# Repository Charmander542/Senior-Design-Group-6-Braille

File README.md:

# Senior Design Group 6 - Braille Project

Welcome to the EC463 Senior Design Group 6 Braille project repository.

Main Google Doc before README migration: https://docs.google.com/document/d/1c1Lonarr0yz-ggmuZfPKdth9k53kwFiAMk2oVoeEsT8/edit?usp=sharing

## Project Structure

### 📁 `electrical/`
Contains hardware-related files including:
- **driver.cpp**: Driver code for hardware control
- **pcb/**: PCB design files
  - `conductors/`: Braille cell conductor board designs (KiCad files)
  - `controller/`: Braille cell controller board designs (KiCad files)
  - `devboard/`: Development board schematics

### 📚 `braille_converter/`
A Python library for converting text to 6-dot braille representation.

**Features:**
- ✨ Convert text to Unicode braille characters
- 📁 Convert entire text files to braille
- 🔍 Detailed character-by-character analysis
- 📊 Visual dot pattern representation
- 🎯 Full support for letters, numbers, punctuation, and symbols

**Quick Start:**
```python
from braille_converter import text_to_braille

text = "Hello World!"
braille = text_to_braille(text)
print(braille)  # Output: ⠠⠓⠑⠇⠇⠕⠀⠠⠺⠕⠗⠇⠙⠖
```

**Documentation:**
- [Full README](braille_converter/README.md) - Complete API documentation
- [Quick Start Guide](braille_converter/QUICKSTART.md) - Get started in 5 minutes
- [Examples](braille_converter/examples/) - Working code examples

**Try it now:**
```bash
cd braille_converter
python demo.py
```

### 🤖 `braille_converter/arduino_library/`
**NEW!** Arduino C++ library for on-device 8-dot Braille conversion - no Python required!

**Features:**
- ⚡ Native Arduino C++ implementation
- 8️⃣ Full 8-dot Braille support (2x4 grid)
- 🔌 Direct hardware control - no computer needed
- 💾 Memory efficient - runs on Arduino Uno
- 🎯 Complete ASCII character set
- 📚 Multiple examples included

**Quick Start:**
```cpp
#include <BrailleConverter.h>

BrailleConverter converter;

void setup() {
  Serial.begin(115200);
  BrailleChar bc = converter.convertChar('A');
  // bc.dots = {1, 7} - ready to drive hardware!
}
```

**Documentation:**
- [Arduino Library README](braille_converter/arduino_library/README.md) - Complete guide
- [Installation Guide](braille_converter/arduino_library/INSTALLATION.md) - Setup instructions
- [Quick Reference](braille_converter/arduino_library/QUICK_REFERENCE.md) - API cheat sheet
- [Examples](braille_converter/arduino_library/examples/) - 4 working examples

### 🔌 `braille_converter/arduino_integration/`
Arduino integration for sending braille patterns to hardware over serial.

**Features:**
- 🔌 Serial communication with Arduino
- 📡 Send braille dot patterns to hardware
- 🎮 Interactive and command-line interfaces
- 🧪 Comprehensive test suite
- 📖 Full examples and documentation

**Quick Test:**
```bash
# Install PySerial
pip install pyserial

# Upload arduino_receiver.ino to your Arduino

# Run interactive mode
cd braille_converter/arduino_integration
python braille_to_arduino.py
```

**Documentation:**
- [Arduino Integration README](braille_converter/arduino_integration/README.md) - Complete guide
- Arduino sketch included (`arduino_receiver.ino`)
- 10+ working examples

## Getting Started

### For Software Development (Braille Converter)
```bash
# Install the library
pip install -e braille_converter

# Run the demo
cd braille_converter
python demo.py

# Run examples
cd braille_converter/examples
python basic_usage.py
python file_conversion.py
```

### For Arduino Integration (Python-based)
```bash
# Install PySerial
pip install pyserial

# 1. Upload arduino_receiver.ino to your Arduino using Arduino IDE

# 2. Find your Arduino port
cd braille_converter/arduino_integration
python braille_to_arduino.py --list

# 3. Run interactive mode
python braille_to_arduino.py

# 4. Or run test suite
python test_arduino.py

# 5. Or run examples
python examples.py
```

See [Arduino Integration README](braille_converter/arduino_integration/README.md) for detailed setup.

### For Arduino Library (Native C++ - No Python Required!)
```bash
# 1. Copy arduino_library folder to Arduino libraries directory
cp -r braille_converter/arduino_library ~/Documents/Arduino/libraries/BrailleConverter

# 2. Restart Arduino IDE

# 3. Open example: File → Examples → BrailleConverter → BasicConversion

# 4. Upload to your Arduino and open Serial Monitor (115200 baud)
```

See [Arduino Library Installation](braille_converter/arduino_library/INSTALLATION.md) for detailed setup.

### For Hardware Development
Navigate to the `electrical/` directory to access:
- PCB design files (KiCad format)
- Hardware driver code
- Development board schematics

## Team

EC463 Senior Design - Group 6

## License

This project is part of the EC463 Senior Design course.

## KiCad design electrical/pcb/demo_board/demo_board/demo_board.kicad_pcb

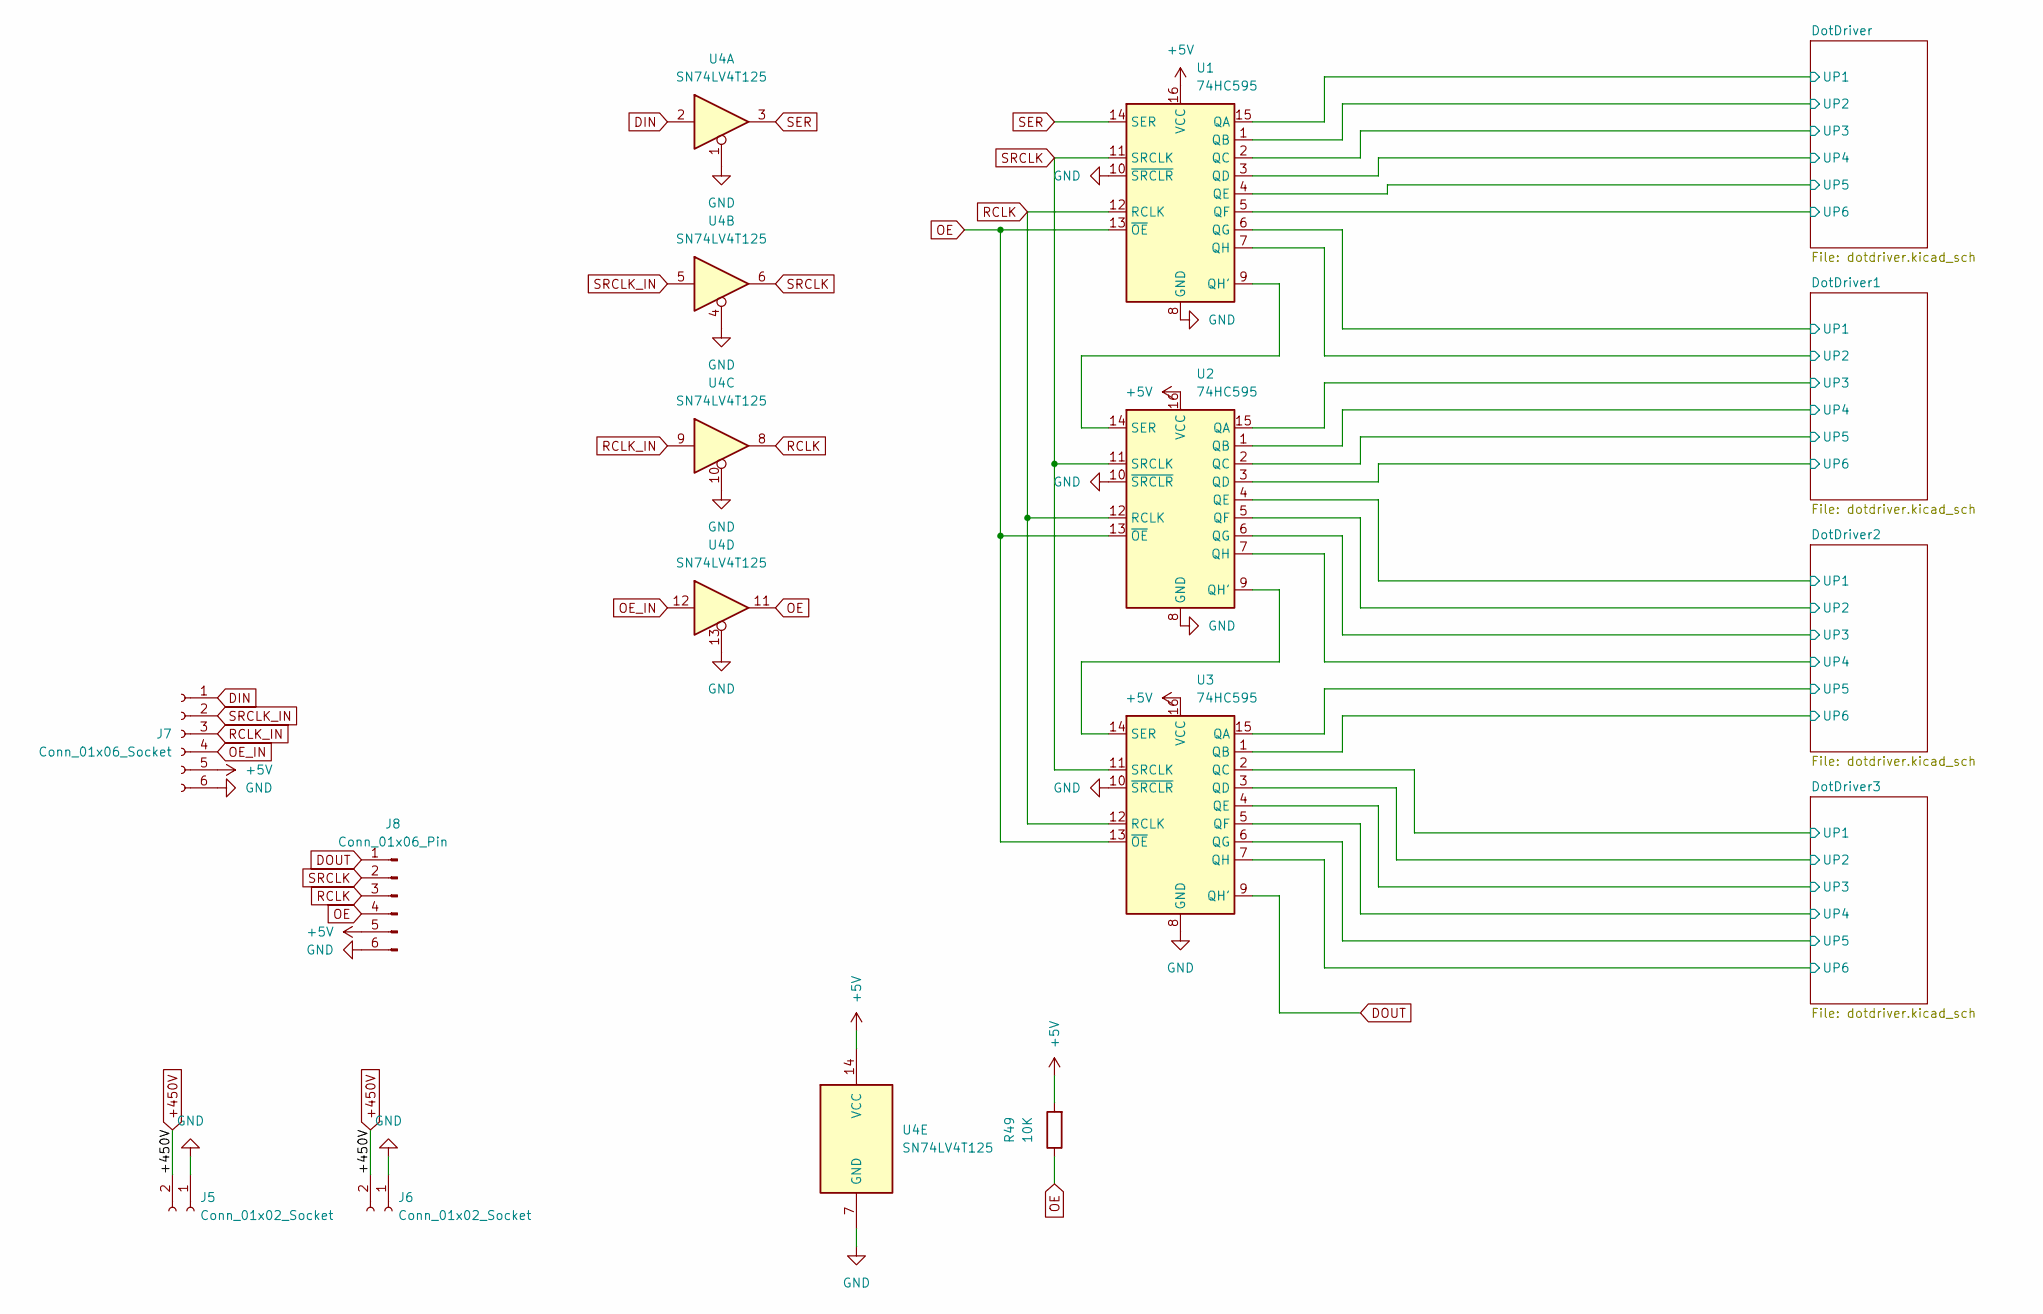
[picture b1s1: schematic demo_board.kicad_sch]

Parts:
J5, J6: Conn_01x02_Socket; AMASS_XT60-M_1x02_P7.20mm_Vertical
J7: Conn_01x06_Socket; PinSocket_2x03_P2.54mm_Horizontal
J8: Conn_01x06_Pin; PinHeader_2x03_P2.54mm_Horizontal
R49: 10K; R_0603_1608Metric
U1, U2, U3: 74HC595; SOIC-16W_5.3x10.2mm_P1.27mm
U4: SN74LV4T125; TSSOP-14_4.4x5mm_P0.65mm

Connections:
+5V: J7.5, J8.5, R49.2, U1.16 (VCC), U2.16 (VCC), U3.16 (VCC), U4.14 (VCC)
+450V: J5.2, J6.2; also elsewhere on the board
/DotDriver1/UP1: U1.6 (QG); also elsewhere on the board
/DotDriver1/UP2: U1.7 (QH); also elsewhere on the board
/DotDriver1/UP3: U2.15 (QA); also elsewhere on the board
/DotDriver1/UP4: U2.1 (QB); also elsewhere on the board
/DotDriver1/UP5: U2.2 (QC); also elsewhere on the board
/DotDriver1/UP6: U2.3 (QD); also elsewhere on the board
/DotDriver2/UP1: U2.4 (QE); also elsewhere on the board
/DotDriver2/UP2: U2.5 (QF); also elsewhere on the board
/DotDriver2/UP3: U2.6 (QG); also elsewhere on the board
/DotDriver2/UP4: U2.7 (QH); also elsewhere on the board
/DotDriver2/UP5: U3.15 (QA); also elsewhere on the board
/DotDriver2/UP6: U3.1 (QB); also elsewhere on the board
/DotDriver3/UP1: U3.2 (QC); also elsewhere on the board
/DotDriver3/UP2: U3.3 (QD); also elsewhere on the board
/DotDriver3/UP3: U3.4 (QE); also elsewhere on the board
/DotDriver3/UP4: U3.5 (QF); also elsewhere on the board
/DotDriver3/UP5: U3.6 (QG); also elsewhere on the board
/DotDriver3/UP6: U3.7 (QH); also elsewhere on the board
/DotDriver/UP1: U1.15 (QA); also elsewhere on the board
/DotDriver/UP2: U1.1 (QB); also elsewhere on the board
/DotDriver/UP3: U1.2 (QC); also elsewhere on the board
/DotDriver/UP4: U1.3 (QD); also elsewhere on the board
/DotDriver/UP5: U1.4 (QE); also elsewhere on the board
/DotDriver/UP6: U1.5 (QF); also elsewhere on the board
DIN: J7.1, U4.2
DOUT: J8.1, U3.9 (QH')
GND: J5.1, J6.1, J7.6, J8.6, U1.8 (GND), U1.10 (~SRCLR), U2.8 (GND), U2.10 (~SRCLR), U3.8 (GND), U3.10 (~SRCLR), U4.1, U4.4, U4.7 (GND), U4.10, U4.13; also elsewhere on the board
unnamed: U1.9 (QH'), U2.14 (SER)
unnamed: U2.9 (QH'), U3.14 (SER)
OE: J8.4, R49.1, U1.13 (~OE), U2.13 (~OE), U3.13 (~OE), U4.11
OE_IN: J7.4, U4.12
RCLK: J8.3, U1.12 (RCLK), U2.12 (RCLK), U3.12 (RCLK), U4.8
RCLK_IN: J7.3, U4.9
SER: U1.14 (SER), U4.3
SRCLK: J8.2, U1.11 (SRCLK), U2.11 (SRCLK), U3.11 (SRCLK), U4.6
SRCLK_IN: J7.2, U4.5

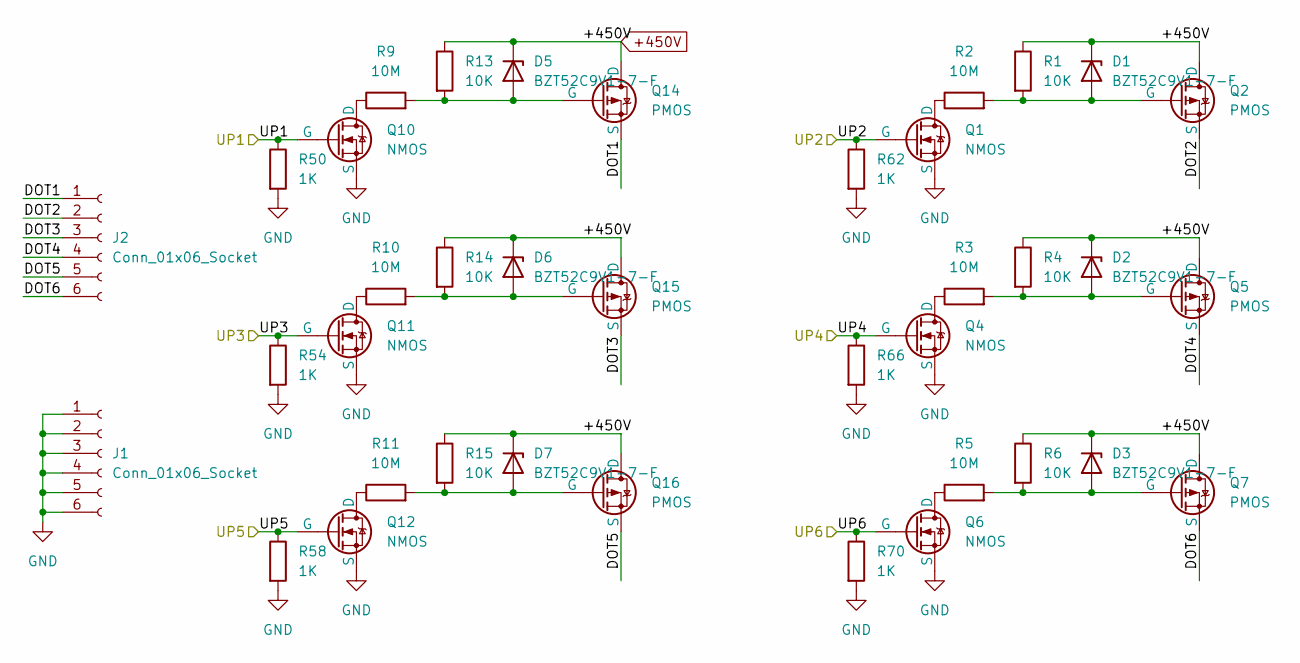
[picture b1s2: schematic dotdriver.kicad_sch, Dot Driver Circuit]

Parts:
D1, D2, D3, D5, D6, D7: BZT52C9V1-7-F; D_SOD-123
J1, J2: Conn_01x06_Socket; PinSocket_2x03_P2.54mm_Vertical
Q1, Q4, Q6, Q10, Q11, Q12: NMOS; SOT-89-3
Q2, Q5, Q7, Q14, Q15, Q16: PMOS; SOT-89-3
R1, R4, R6, R13, R14, R15: 10K; R_0603_1608Metric
R2, R3, R5, R9, R10, R11: 10M; R_0603_1608Metric
R50, R54, R58, R62, R66, R70: 1K; R_0603_1608Metric

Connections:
+450V: D1.1 (K), D2.1 (K), D3.1 (K), D5.1 (K), D6.1 (K), D7.1 (K), Q2.1 (D), Q5.1 (D), Q7.1 (D), Q14.1 (D), Q15.1 (D), Q16.1 (D), R1.1, R4.1, R6.1, R13.1, R14.1, R15.1; also elsewhere on the board
/DotDriver/DOT1: J2.1, Q14.3 (S)
/DotDriver/DOT2: J2.2, Q2.3 (S)
/DotDriver/DOT3: J2.3, Q15.3 (S)
/DotDriver/DOT4: J2.4, Q5.3 (S)
/DotDriver/DOT5: J2.5, Q16.3 (S)
/DotDriver/DOT6: J2.6, Q7.3 (S)
/DotDriver/UP1: Q10.2 (G), R50.1; also elsewhere on the board
/DotDriver/UP2: Q1.2 (G), R62.1; also elsewhere on the board
/DotDriver/UP3: Q11.2 (G), R54.1; also elsewhere on the board
/DotDriver/UP4: Q4.2 (G), R66.1; also elsewhere on the board
/DotDriver/UP5: Q12.2 (G), R58.1; also elsewhere on the board
/DotDriver/UP6: Q6.2 (G), R70.1; also elsewhere on the board
GND: J1.1, J1.2, J1.3, J1.4, J1.5, J1.6, Q1.3 (S), Q4.3 (S), Q6.3 (S), Q10.3 (S), Q11.3 (S), Q12.3 (S), R50.2, R54.2, R58.2, R62.2, R66.2, R70.2; also elsewhere on the board
unnamed: D1.2 (A), Q2.2 (G), R1.2, R2.2
unnamed: D2.2 (A), Q5.2 (G), R3.2, R4.2
unnamed: D3.2 (A), Q7.2 (G), R5.2, R6.2
unnamed: D5.2 (A), Q14.2 (G), R9.2, R13.2
unnamed: D6.2 (A), Q15.2 (G), R10.2, R14.2
unnamed: D7.2 (A), Q16.2 (G), R11.2, R15.2
unnamed: Q1.1 (D), R2.1
unnamed: Q4.1 (D), R3.1
unnamed: Q6.1 (D), R5.1
unnamed: Q10.1 (D), R9.1
unnamed: Q11.1 (D), R10.1
unnamed: Q12.1 (D), R11.1

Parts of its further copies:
D4, D8, D9, D10, D11, D12, D13, D14, D15, D16, D17, D18, D19, D20, D21, D22, D23, D24: BZT52C9V1-7-F; D_SOD-123
J0, J3, J4, J9, J10, J11: Conn_01x06_Socket; PinSocket_2x03_P2.54mm_Vertical
Q3, Q8, Q9, Q19, Q20, Q21, Q25, Q26, Q27, Q31, Q32, Q33, Q37, Q38, Q39, Q43, Q44, Q45: NMOS; SOT-89-3
Q13, Q17, Q18, Q22, Q23, Q24, Q28, Q29, Q30, Q34, Q35, Q36, Q40, Q41, Q42, Q46, Q47, Q48: PMOS; SOT-89-3
R7, R8, R12, R19, R20, R21, R25, R26, R27, R31, R32, R33, R37, R38, R39, R43, R44, R45: 10M; R_0603_1608Metric
R16, R17, R18, R22, R23, R24, R28, R29, R30, R34, R35, R36, R40, R41, R42, R46, R47, R48: 10K; R_0603_1608Metric
R51, R52, R53, R55, R56, R57, R59, R60, R61, R63, R64, R65, R67, R68, R69, R71, R72, R73: 1K; R_0603_1608Metric

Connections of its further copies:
+450V: D4.1 (K), D8.1 (K), D9.1 (K), D10.1 (K), D11.1 (K), D12.1 (K), D13.1 (K), D14.1 (K), D15.1 (K), D16.1 (K), D17.1 (K), D18.1 (K), D19.1 (K), D20.1 (K), D21.1 (K), D22.1 (K), D23.1 (K), D24.1 (K), Q13.1 (D), Q17.1 (D), Q18.1 (D), Q22.1 (D), Q23.1 (D), Q24.1 (D), Q28.1 (D), Q29.1 (D), Q30.1 (D), Q34.1 (D), Q35.1 (D), Q36.1 (D), Q40.1 (D), Q41.1 (D), Q42.1 (D), Q46.1 (D), Q47.1 (D), Q48.1 (D), R16.1, R17.1, R18.1, R22.1, R23.1, R24.1, R28.1, R29.1, R30.1, R34.1, R35.1, R36.1, R40.1, R41.1, R42.1, R46.1, R47.1, R48.1; also elsewhere on the board
/DotDriver1/DOT1: J0.1, Q13.3 (S)
/DotDriver1/DOT2: J0.2, Q22.3 (S)
/DotDriver1/DOT3: J0.3, Q17.3 (S)
/DotDriver1/DOT4: J0.4, Q23.3 (S)
/DotDriver1/DOT5: J0.5, Q18.3 (S)
/DotDriver1/DOT6: J0.6, Q24.3 (S)
/DotDriver1/UP1: Q3.2 (G), R51.1; also elsewhere on the board
/DotDriver1/UP2: Q19.2 (G), R63.1; also elsewhere on the board
/DotDriver1/UP3: Q8.2 (G), R55.1; also elsewhere on the board
/DotDriver1/UP4: Q20.2 (G), R67.1; also elsewhere on the board
/DotDriver1/UP5: Q9.2 (G), R59.1; also elsewhere on the board
/DotDriver1/UP6: Q21.2 (G), R71.1; also elsewhere on the board
/DotDriver2/DOT1: J3.1, Q28.3 (S)
/DotDriver2/DOT2: J3.2, Q34.3 (S)
/DotDriver2/DOT3: J3.3, Q29.3 (S)
/DotDriver2/DOT4: J3.4, Q35.3 (S)
/DotDriver2/DOT5: J3.5, Q30.3 (S)
/DotDriver2/DOT6: J3.6, Q36.3 (S)
/DotDriver2/UP1: Q25.2 (G), R52.1; also elsewhere on the board
/DotDriver2/UP2: Q31.2 (G), R64.1; also elsewhere on the board
/DotDriver2/UP3: Q26.2 (G), R56.1; also elsewhere on the board
/DotDriver2/UP4: Q32.2 (G), R68.1; also elsewhere on the board
/DotDriver2/UP5: Q27.2 (G), R60.1; also elsewhere on the board
/DotDriver2/UP6: Q33.2 (G), R72.1; also elsewhere on the board
/DotDriver3/DOT1: J4.1, Q40.3 (S)
/DotDriver3/DOT2: J4.2, Q46.3 (S)
/DotDriver3/DOT3: J4.3, Q41.3 (S)
/DotDriver3/DOT4: J4.4, Q47.3 (S)
/DotDriver3/DOT5: J4.5, Q42.3 (S)
/DotDriver3/DOT6: J4.6, Q48.3 (S)
/DotDriver3/UP1: Q37.2 (G), R53.1; also elsewhere on the board
/DotDriver3/UP2: Q43.2 (G), R65.1; also elsewhere on the board
/DotDriver3/UP3: Q38.2 (G), R57.1; also elsewhere on the board
/DotDriver3/UP4: Q44.2 (G), R69.1; also elsewhere on the board
/DotDriver3/UP5: Q39.2 (G), R61.1; also elsewhere on the board
/DotDriver3/UP6: Q45.2 (G), R73.1; also elsewhere on the board
GND: J9.1, J9.2, J9.3, J9.4, J9.5, J9.6, J10.1, J10.2, J10.3, J10.4, J10.5, J10.6, J11.1, J11.2, J11.3, J11.4, J11.5, J11.6, Q3.3 (S), Q8.3 (S), Q9.3 (S), Q19.3 (S), Q20.3 (S), Q21.3 (S), Q25.3 (S), Q26.3 (S), Q27.3 (S), Q31.3 (S), Q32.3 (S), Q33.3 (S), Q37.3 (S), Q38.3 (S), Q39.3 (S), Q43.3 (S), Q44.3 (S), Q45.3 (S), R51.2, R52.2, R53.2, R55.2, R56.2, R57.2, R59.2, R60.2, R61.2, R63.2, R64.2, R65.2, R67.2, R68.2, R69.2, R71.2, R72.2, R73.2; also elsewhere on the board
unnamed: D4.2 (A), Q13.2 (G), R7.2, R16.2
unnamed: D8.2 (A), Q17.2 (G), R8.2, R17.2
unnamed: D9.2 (A), Q18.2 (G), R12.2, R18.2
unnamed: D10.2 (A), Q22.2 (G), R19.2, R22.2
unnamed: D11.2 (A), Q23.2 (G), R20.2, R23.2
unnamed: D12.2 (A), Q24.2 (G), R21.2, R24.2
unnamed: D13.2 (A), Q28.2 (G), R25.2, R28.2
unnamed: D14.2 (A), Q29.2 (G), R26.2, R29.2
unnamed: D15.2 (A), Q30.2 (G), R27.2, R30.2
unnamed: D16.2 (A), Q34.2 (G), R31.2, R34.2
unnamed: D17.2 (A), Q35.2 (G), R32.2, R35.2
unnamed: D18.2 (A), Q36.2 (G), R33.2, R36.2
unnamed: D19.2 (A), Q40.2 (G), R37.2, R40.2
unnamed: D20.2 (A), Q41.2 (G), R38.2, R41.2
unnamed: D21.2 (A), Q42.2 (G), R39.2, R42.2
unnamed: D22.2 (A), Q46.2 (G), R43.2, R46.2
unnamed: D23.2 (A), Q47.2 (G), R44.2, R47.2
unnamed: D24.2 (A), Q48.2 (G), R45.2, R48.2
unnamed: Q3.1 (D), R7.1
unnamed: Q8.1 (D), R8.1
unnamed: Q9.1 (D), R12.1
unnamed: Q19.1 (D), R19.1
unnamed: Q20.1 (D), R20.1
unnamed: Q21.1 (D), R21.1
unnamed: Q25.1 (D), R25.1
unnamed: Q26.1 (D), R26.1
unnamed: Q27.1 (D), R27.1
unnamed: Q31.1 (D), R31.1
unnamed: Q32.1 (D), R32.1
unnamed: Q33.1 (D), R33.1
unnamed: Q37.1 (D), R37.1
unnamed: Q38.1 (D), R38.1
unnamed: Q39.1 (D), R39.1
unnamed: Q43.1 (D), R43.1
unnamed: Q44.1 (D), R44.1
unnamed: Q45.1 (D), R45.1

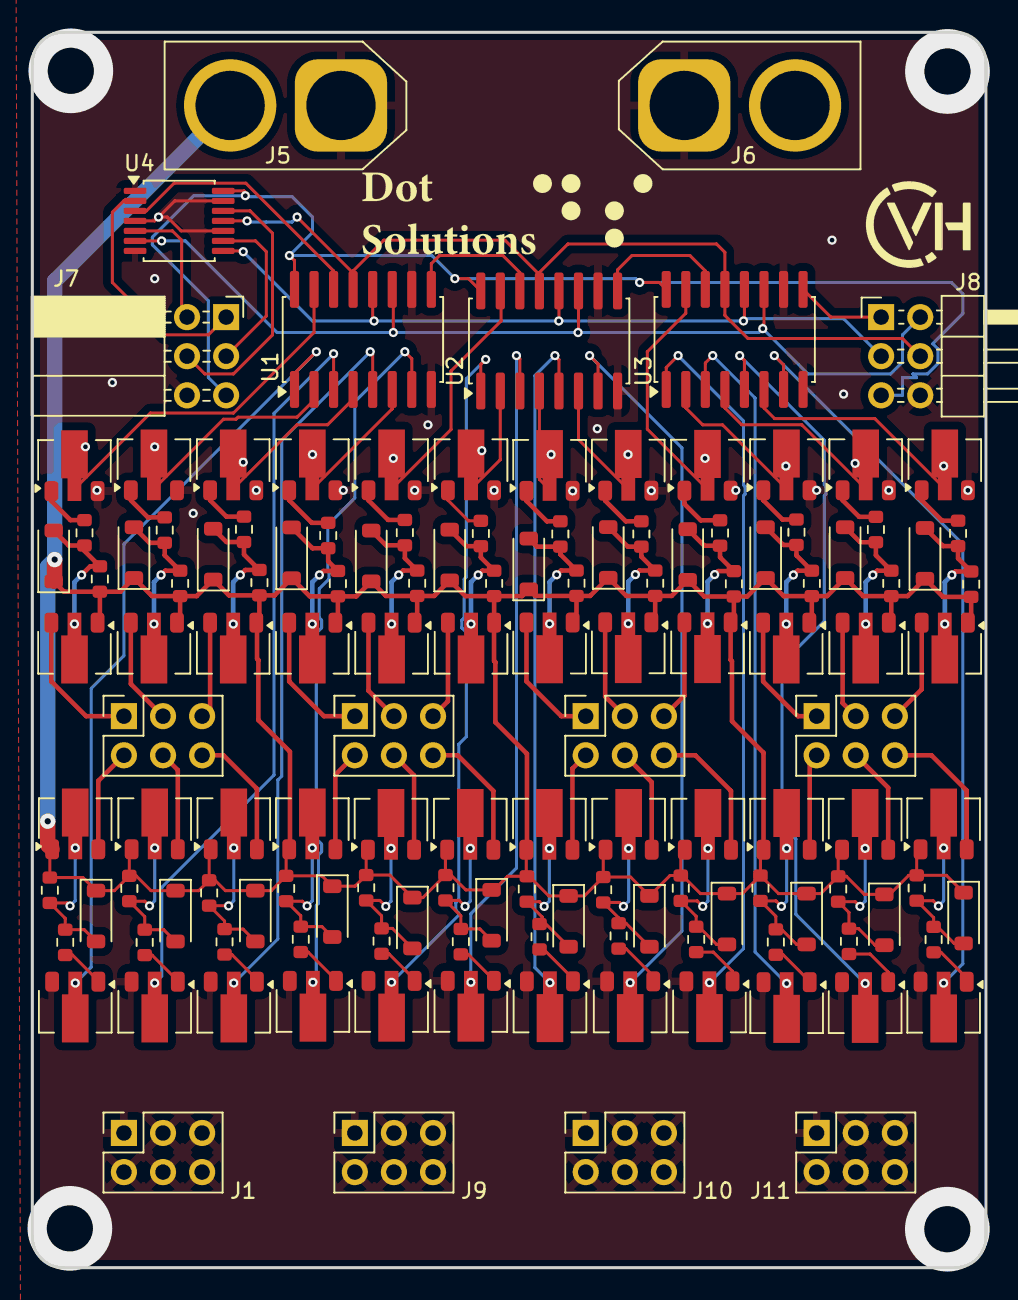
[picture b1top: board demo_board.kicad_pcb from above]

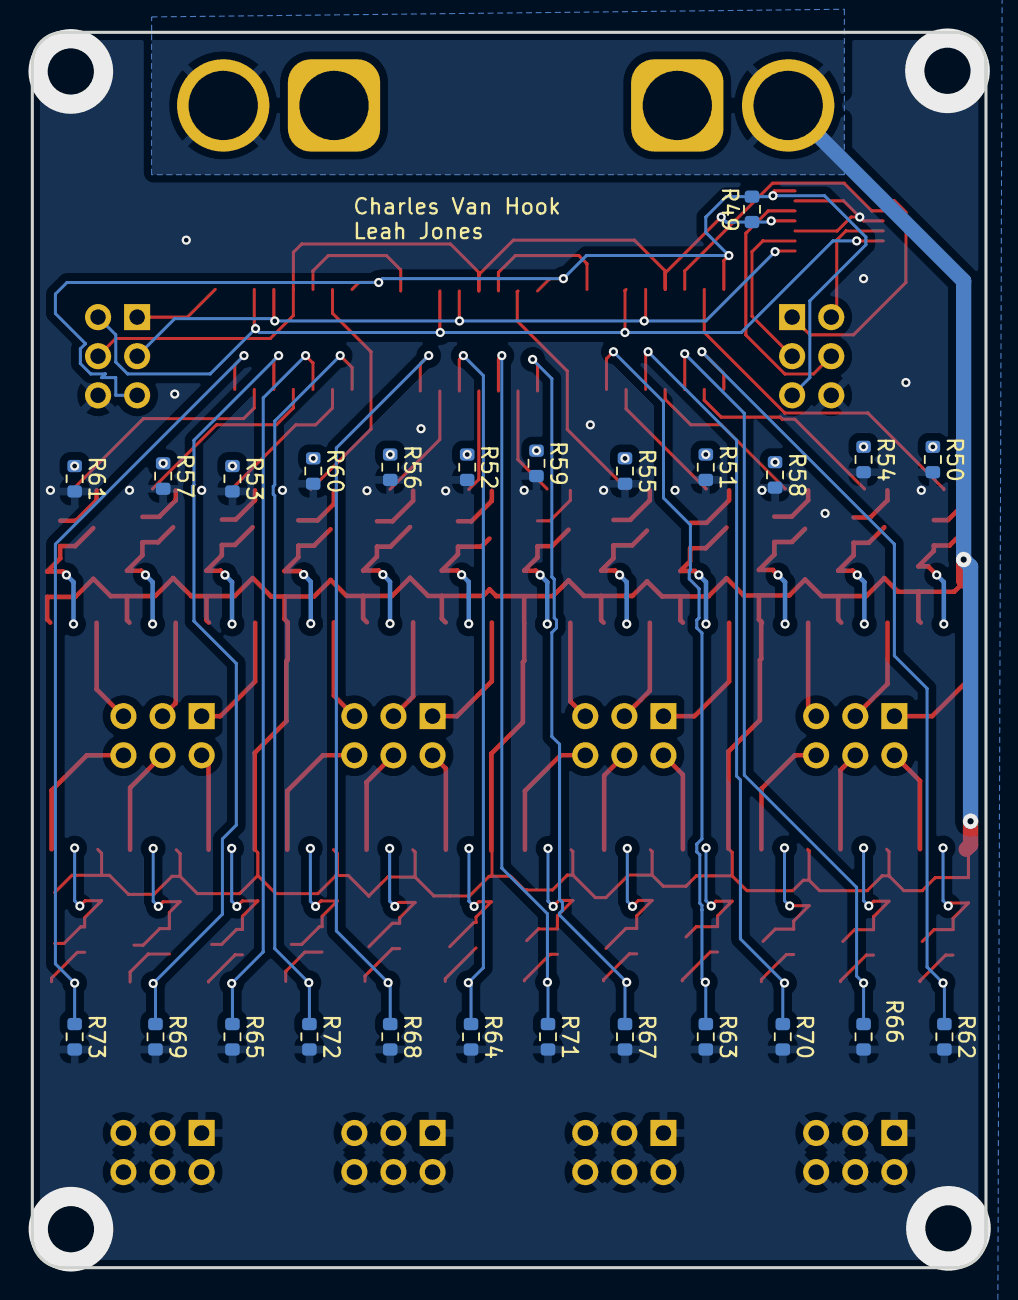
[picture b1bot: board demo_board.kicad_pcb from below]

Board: 2 copper layers, 62.0 x 80.2 mm, 161 parts (25 on the bottom side), 110 nets.

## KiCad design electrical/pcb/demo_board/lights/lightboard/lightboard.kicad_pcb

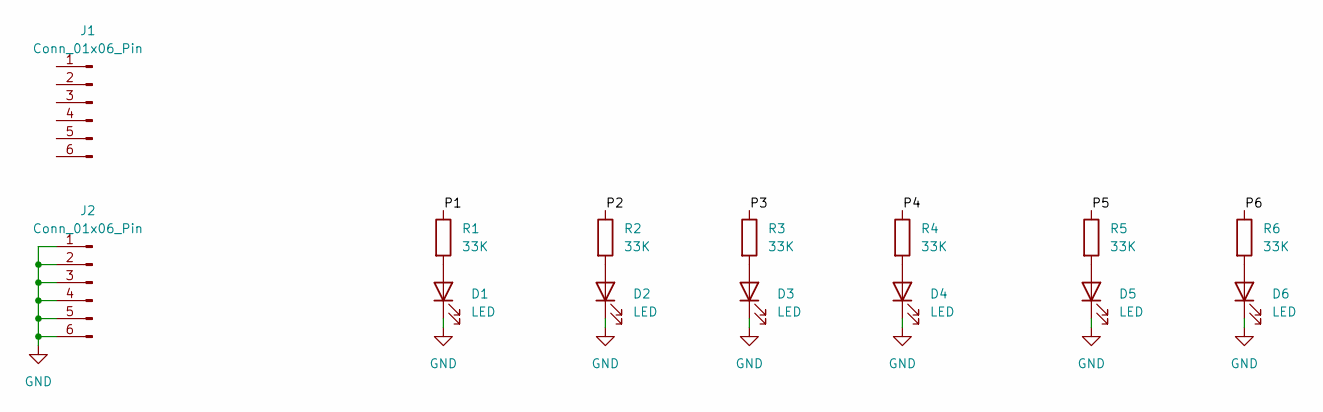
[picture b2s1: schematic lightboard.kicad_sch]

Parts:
D1, D2, D3, D4, D5, D6: LED; LED_0805_2012Metric
J1, J2: Conn_01x06_Pin
R1, R2, R3, R4, R5, R6: 33K; R_1210_3225Metric

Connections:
/P1: J1.6, R1.1
/P2: J1.1, R2.1
/P3: J1.3, R3.1
/P4: J1.4, R4.1
/P5: J1.2, R5.1
/P6: J1.5, R6.1
GND: D1.1 (K), D2.1 (K), D3.1 (K), D4.1 (K), D5.1 (K), D6.1 (K), J2.1, J2.2, J2.3, J2.4, J2.5, J2.6
unnamed: D1.2 (A), R1.2
unnamed: D2.2 (A), R2.2
unnamed: D3.2 (A), R3.2
unnamed: D4.2 (A), R4.2
unnamed: D5.2 (A), R5.2
unnamed: D6.2 (A), R6.2

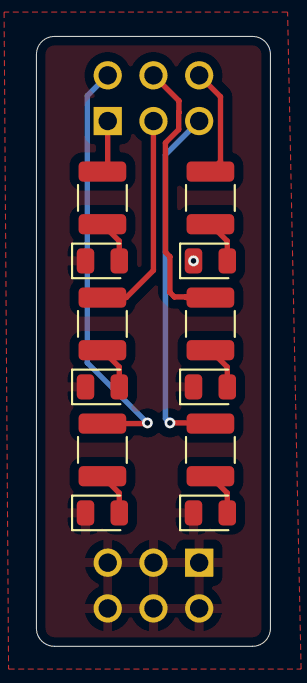
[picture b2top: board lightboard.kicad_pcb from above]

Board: 2 copper layers, 13.0 x 33.9 mm, 14 parts (0 on the bottom side), 13 nets.

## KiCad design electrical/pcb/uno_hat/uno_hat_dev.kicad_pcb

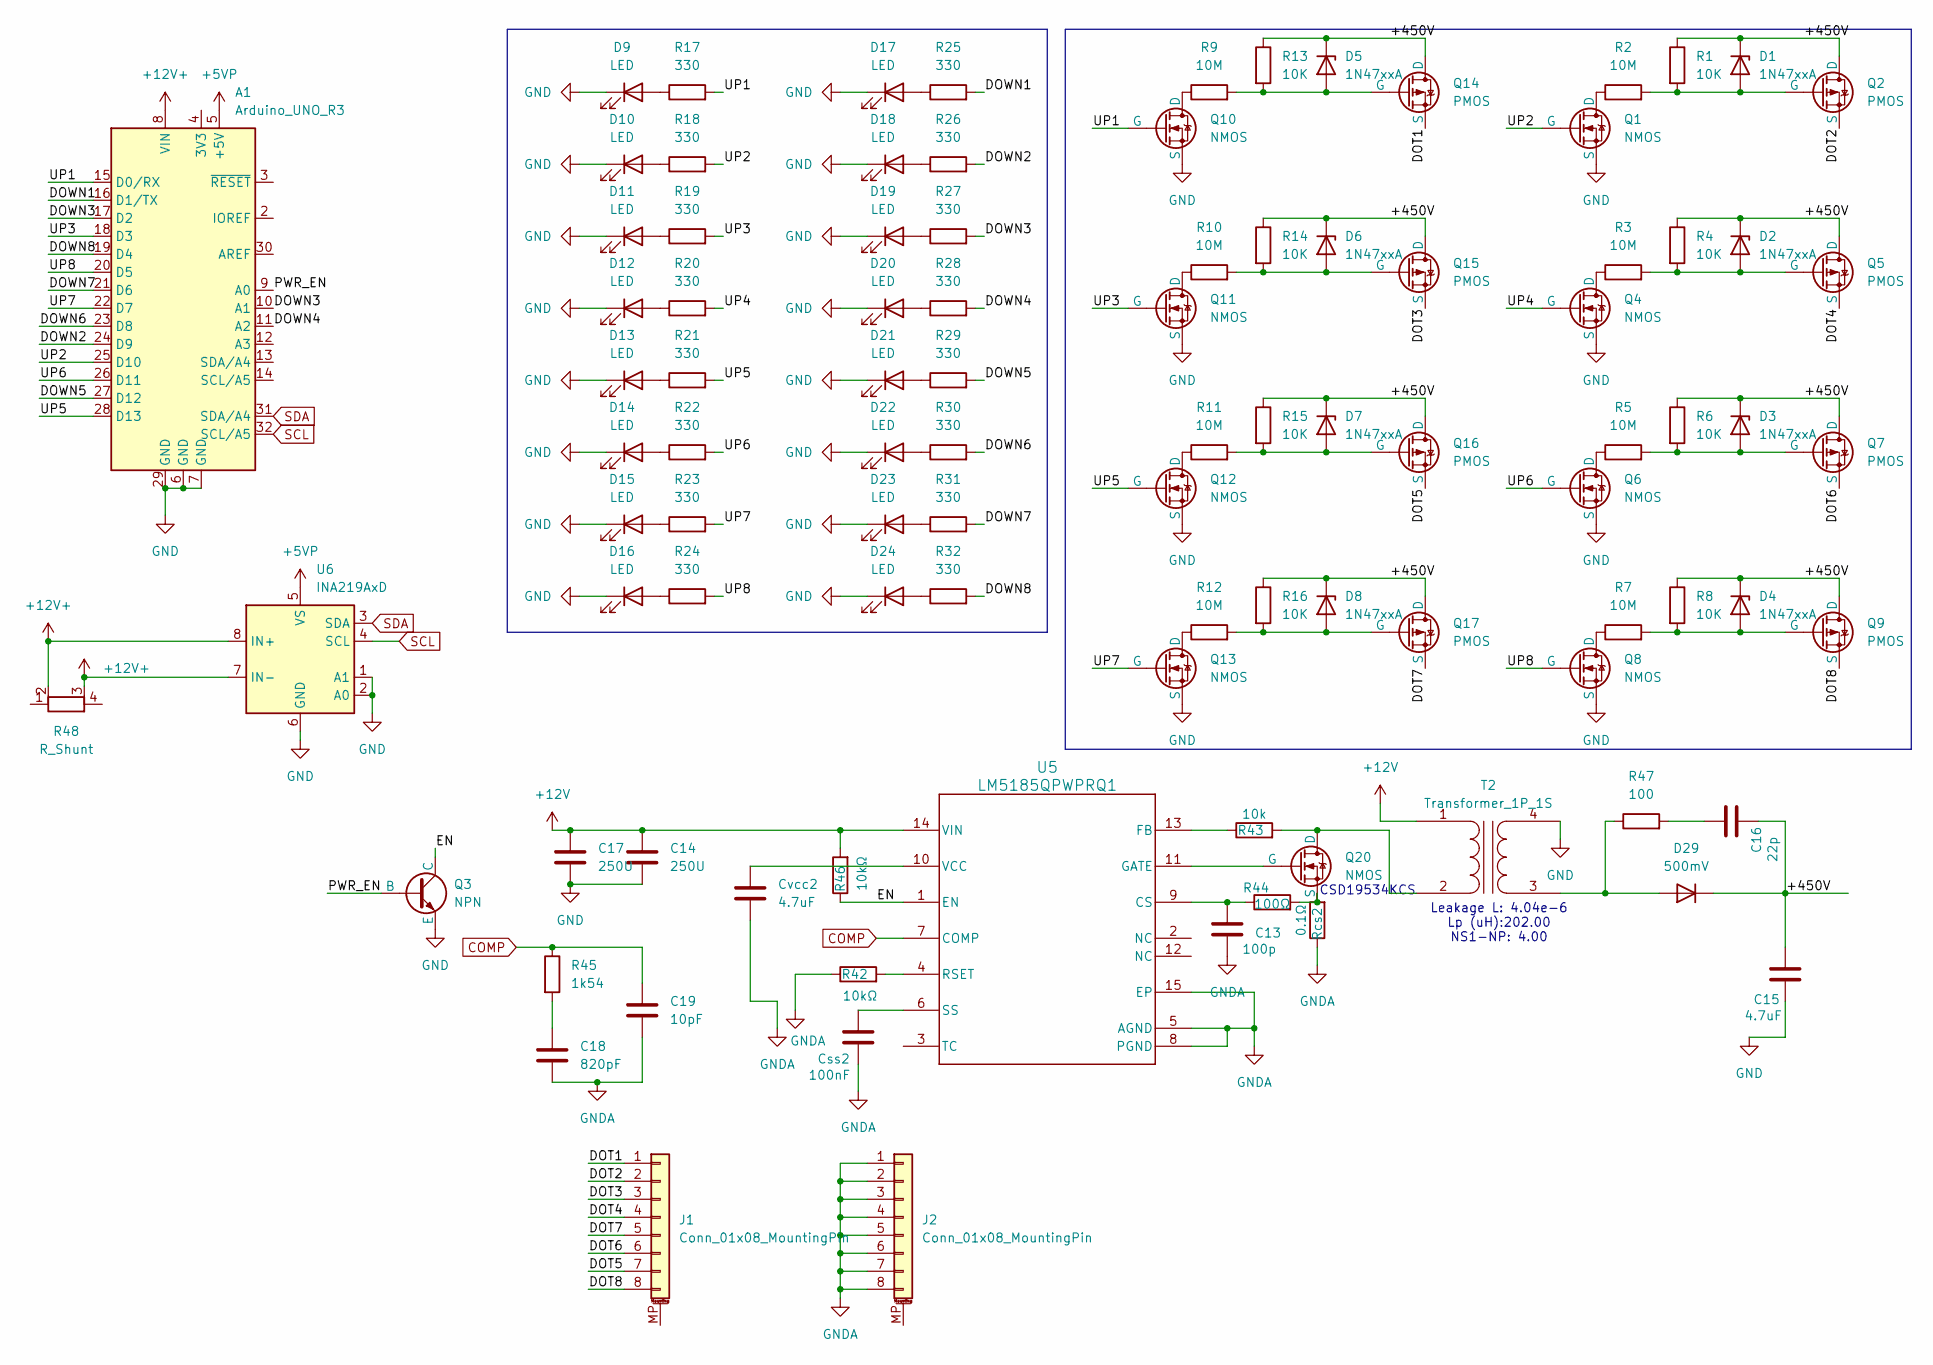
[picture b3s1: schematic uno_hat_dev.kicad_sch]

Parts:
A1: Arduino_UNO_R3
C13: 100p; R_0805_2012Metric
C14, C17: 250U; CP_Radial_Tantal_D8.0mm_P2.50mm
C15: 4.7uF; R_0805_2012Metric
C16: 22p; R_0805_2012Metric
C18: 820pF; R_0805_2012Metric
C19: 10pF; R_0805_2012Metric
Css2: 100nF; R_0805_2012Metric
Cvcc2: 4.7uF; R_0805_2012Metric
D1, D2, D3, D4, D5, D6, D7, D8: 1N47xxA; D_DO-41_SOD81_P10.16mm_Horizontal
D9, D10, D11, D12, D13, D14, D15, D16, D17, D18, D19, D20, D21, D22, D23, D24: LED; LED_0805_2012Metric
D29: 500mV; D_A-405_P12.70mm_Horizontal
J1, J2: Conn_01x08_MountingPin; Amphenol_F32Q-1A7x1-11008_1x08-1MP_P0.5mm_Horizontal
Q1, Q4, Q6, Q8, Q10, Q11, Q12, Q13: NMOS; TO-92_Inline
Q2, Q5, Q7, Q9, Q14, Q15, Q16, Q17: PMOS; TO-92_Inline
Q3: NPN; TO-92_Inline
Q20: NMOS; TO-220-3_Vertical
R1, R4, R6, R8, R13, R14, R15, R16: 10K; R_Axial_DIN0207_L6.3mm_D2.5mm_P7.62mm_Horizontal
R2, R3, R5, R7, R9, R10, R11, R12: 10M; R_Axial_DIN0207_L6.3mm_D2.5mm_P7.62mm_Horizontal
R17, R18, R19, R20, R21, R22, R23, R24, R25, R26, R27, R28, R29, R30, R31, R32: 330; R_0805_2012Metric
R42, R46: 10kΩ; R_0805_2012Metric
R43: 10k; R_0805_2012Metric
R44: 100Ω; R_0805_2012Metric
R45: 1k54; R_0805_2012Metric
R47: 100; R_0805_2012Metric
R48: R_Shunt; R_Shunt_Ohmite_LVK24
Rcs2: 0.1Ω; R_0805_2012Metric
T2: Transformer_1P_1S; PinSocket_1x04_P2.54mm_Vertical
U5: LM5185QPWPRQ1; Texas_HTSSOP-14-1EP_4.4x5mm_P0.65mm_EP3.4x5mm_Mask3.155x3.2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
U6: INA219AxD; SOIC-8_3.9x4.9mm_P1.27mm

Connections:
+5VP: A1.5 (+5V), U6.5 (VS)
+12V: C14.1, C17.1, R46.2, T2.1 (AA), U5.14 (VIN)
+12V+: A1.8 (VIN), R48.2, R48.3, U6.7 (IN-), U6.8 (IN+)
/+450V: C15.1, C16.2, D1.1 (K), D2.1 (K), D3.1 (K), D4.1 (K), D5.1 (K), D6.1 (K), D7.1 (K), D8.1 (K), D29.1 (K), Q2.1 (D), Q5.1 (D), Q7.1 (D), Q9.1 (D), Q14.1 (D), Q15.1 (D), Q16.1 (D), Q17.1 (D), R1.1, R4.1, R6.1, R8.1, R13.1, R14.1, R15.1, R16.1
/DOT1: J1.1, Q14.3 (S)
/DOT2: J1.2, Q2.3 (S)
/DOT3: J1.3, Q15.3 (S)
/DOT4: J1.4, Q5.3 (S)
/DOT5: J1.7, Q16.3 (S)
/DOT6: J1.6, Q7.3 (S)
/DOT7: J1.5, Q17.3 (S)
/DOT8: J1.8, Q9.3 (S)
/DOWN1: A1.16 (D1/TX), R25.2
/DOWN2: A1.24 (D9), R26.2
/DOWN3: A1.10 (A1), A1.17 (D2), R27.2
/DOWN4: A1.11 (A2), R28.2
/DOWN5: A1.27 (D12), R29.2
/DOWN6: A1.23 (D8), R30.2
/DOWN7: A1.21 (D6), R31.2
/DOWN8: A1.19 (D4), R32.2
/EN: Q3.1 (C), R46.1, U5.1 (EN)
/PWR_EN: A1.9 (A0), Q3.2 (B)
/UP1: A1.15 (D0/RX), Q10.2 (G), R17.2
/UP2: A1.25 (D10), Q1.2 (G), R18.2
/UP3: A1.18 (D3), Q11.2 (G), R19.2
/UP4: Q4.2 (G), R20.2
/UP5: A1.28 (D13), Q12.2 (G), R21.2
/UP6: A1.26 (D11), Q6.2 (G), R22.2
/UP7: A1.22 (D7), Q13.2 (G), R23.2
/UP8: A1.20 (D5), Q8.2 (G), R24.2
COMP: C19.1, R45.1, U5.7 (COMP)
GND: A1.6 (GND), A1.7 (GND), A1.29 (GND), C14.2, C15.2, C17.2, D9.1 (K), D10.1 (K), D11.1 (K), D12.1 (K), D13.1 (K), D14.1 (K), D15.1 (K), D16.1 (K), D17.1 (K), D18.1 (K), D19.1 (K), D20.1 (K), D21.1 (K), D22.1 (K), D23.1 (K), D24.1 (K), Q1.3 (S), Q3.3 (E), Q4.3 (S), Q6.3 (S), Q8.3 (S), Q10.3 (S), Q11.3 (S), Q12.3 (S), Q13.3 (S), T2.4 (SB), U6.1 (A1), U6.2 (A0), U6.6 (GND)
GNDA: C13.2, C18.2, C19.2, Css2.2, Cvcc2.2, J2.1, J2.2, J2.3, J2.4, J2.5, J2.6, J2.7, J2.8, R42.1, Rcs2.1, U5.5 (AGND), U5.8 (PGND), U5.15 (EP)
unnamed: C16.1, R47.2
unnamed: C18.1, R45.2
unnamed: D1.2 (A), Q2.2 (G), R1.2, R2.2
unnamed: D2.2 (A), Q5.2 (G), R3.2, R4.2
unnamed: D3.2 (A), Q7.2 (G), R5.2, R6.2
unnamed: D4.2 (A), Q9.2 (G), R7.2, R8.2
unnamed: D5.2 (A), Q14.2 (G), R9.2, R13.2
unnamed: D6.2 (A), Q15.2 (G), R10.2, R14.2
unnamed: D7.2 (A), Q16.2 (G), R11.2, R15.2
unnamed: D8.2 (A), Q17.2 (G), R12.2, R16.2
unnamed: D9.2 (A), R17.1
unnamed: D10.2 (A), R18.1
unnamed: D11.2 (A), R19.1
unnamed: D12.2 (A), R20.1
unnamed: D13.2 (A), R21.1
unnamed: D14.2 (A), R22.1
unnamed: D15.2 (A), R23.1
unnamed: D16.2 (A), R24.1
unnamed: D17.2 (A), R25.1
unnamed: D18.2 (A), R26.1
unnamed: D19.2 (A), R27.1
unnamed: D20.2 (A), R28.1
unnamed: D21.2 (A), R29.1
unnamed: D22.2 (A), R30.1
unnamed: D23.2 (A), R31.1
unnamed: D24.2 (A), R32.1
unnamed: D29.2 (A), R47.1, T2.3 (SA)
unnamed: Q1.1 (D), R2.1
unnamed: Q4.1 (D), R3.1
unnamed: Q6.1 (D), R5.1
unnamed: Q8.1 (D), R7.1
unnamed: Q10.1 (D), R9.1
unnamed: Q11.1 (D), R10.1
unnamed: Q12.1 (D), R11.1
unnamed: Q13.1 (D), R12.1
unnamed: Q20.1 (D), R43.2, T2.2 (AB)
unnamed: Q20.2 (G), U5.11 (GATE)
unnamed: Q20.3 (S), R44.2, Rcs2.2
unnamed: C13.1, R44.1, U5.9 (CS)
unnamed: R43.1, U5.13 (FB)
unnamed: R42.2, U5.4 (RSET)
unnamed: Css2.1, U5.6 (SS)
unnamed: Cvcc2.1, U5.10 (VCC)
SCL: A1.32 (SCL/A5), U6.4 (SCL)
SDA: A1.31 (SDA/A4), U6.3 (SDA)

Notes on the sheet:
Leakage L: 4.04e-6 Lp (uH):202.00 NS1-NP: 4.00
CSD19534KCS

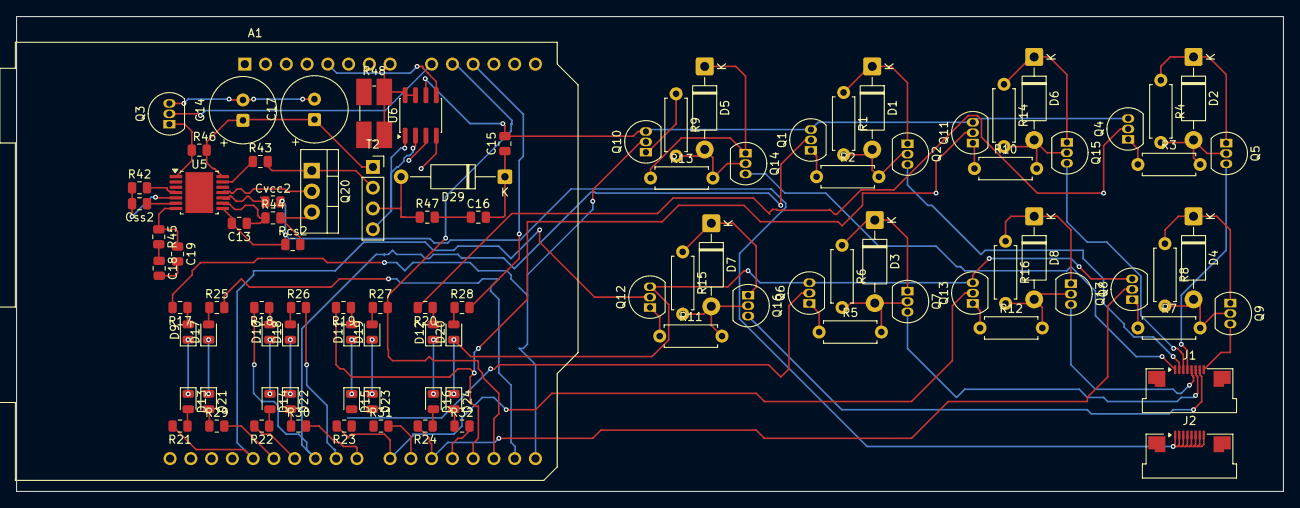
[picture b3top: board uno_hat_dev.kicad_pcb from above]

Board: 2 copper layers, 155.0 x 58.1 mm, 98 parts (0 on the bottom side), 78 nets.

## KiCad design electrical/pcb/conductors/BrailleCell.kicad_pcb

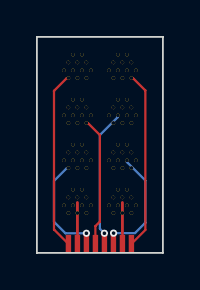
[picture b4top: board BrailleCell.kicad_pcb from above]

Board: 2 copper layers, 7.0 x 12.0 mm, 9 parts (0 on the bottom side), 8 nets.

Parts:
CONDUCTOR: Conn_01x08_Socket; FPC Connecotr
J2, J3, J4, J5, J6, J7, J8, J9: Conn_01x01_Pin; Pump Pin

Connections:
unnamed: CONDUCTOR.1, J2.1
unnamed: CONDUCTOR.2, J3.1
unnamed: CONDUCTOR.3, J4.1
unnamed: CONDUCTOR.4, J5.1
unnamed: CONDUCTOR.5, J6.1
unnamed: CONDUCTOR.6, J7.1
unnamed: CONDUCTOR.7, J8.1
unnamed: CONDUCTOR.8, J9.1
